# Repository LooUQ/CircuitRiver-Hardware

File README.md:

# CircuitRiver-Hardware
Schematics and PCB layouts for LooUQ Circuit River devices

LooUQ designs and manufactures our Circuit River wireless communications products to make your project range far and wide. Featuring advanced long-distance LTE and LoRa wireless technology and efficient integration with leading development systems and MCU architectures.

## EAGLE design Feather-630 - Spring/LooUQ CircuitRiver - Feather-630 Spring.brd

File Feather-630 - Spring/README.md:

# PCB files for the LooUQ Circuit River Feather-630 Spring 

The LooUQ Circuit River Feather-630 Spring device enables a quick and seemless connection between a Feather form development board (such as Adafruit Feather M0 Express, Adafruit Feather M4 Express, or the SparkFun SAMD51 Things Plus) and any of the LooUQ Circuit River Stream wireless communications circuit boards, when your project also needs a flexible power source. The Feather-630 accepts a DC power source from 6-volts to 30-volts. If you don't need this input voltage flexibility, then consider our Feather-5 Spring; it is less expensive.

The Feather-630 Spring is designed to fit neatly in a [Polycase LP-35F](https://www.polycase.com/lp-35f) or unflanged LP-35P. We left you some room to stuff some sensor or other logic in there too.

EagleCAD format schematic and circuit board layout

For more details, check out the [LooUQ website](http://www.loouq.com) or information in our support desk knowledgebase at [LooUQ Answers Support Desk](http://answers.loouq.com).

Designed by LooUQ
GNU General Public License v3.0, please review the LICENSE file for more information. Commercial private licensing is available, please contact LooUQ via our answers.loouq.com support desk.

Feather form-factor is thanks to Adafruit Industries, see https://adafruit.com
Qwiic sensor connection system is thanks to SparkFun, see https://sparkfun.com

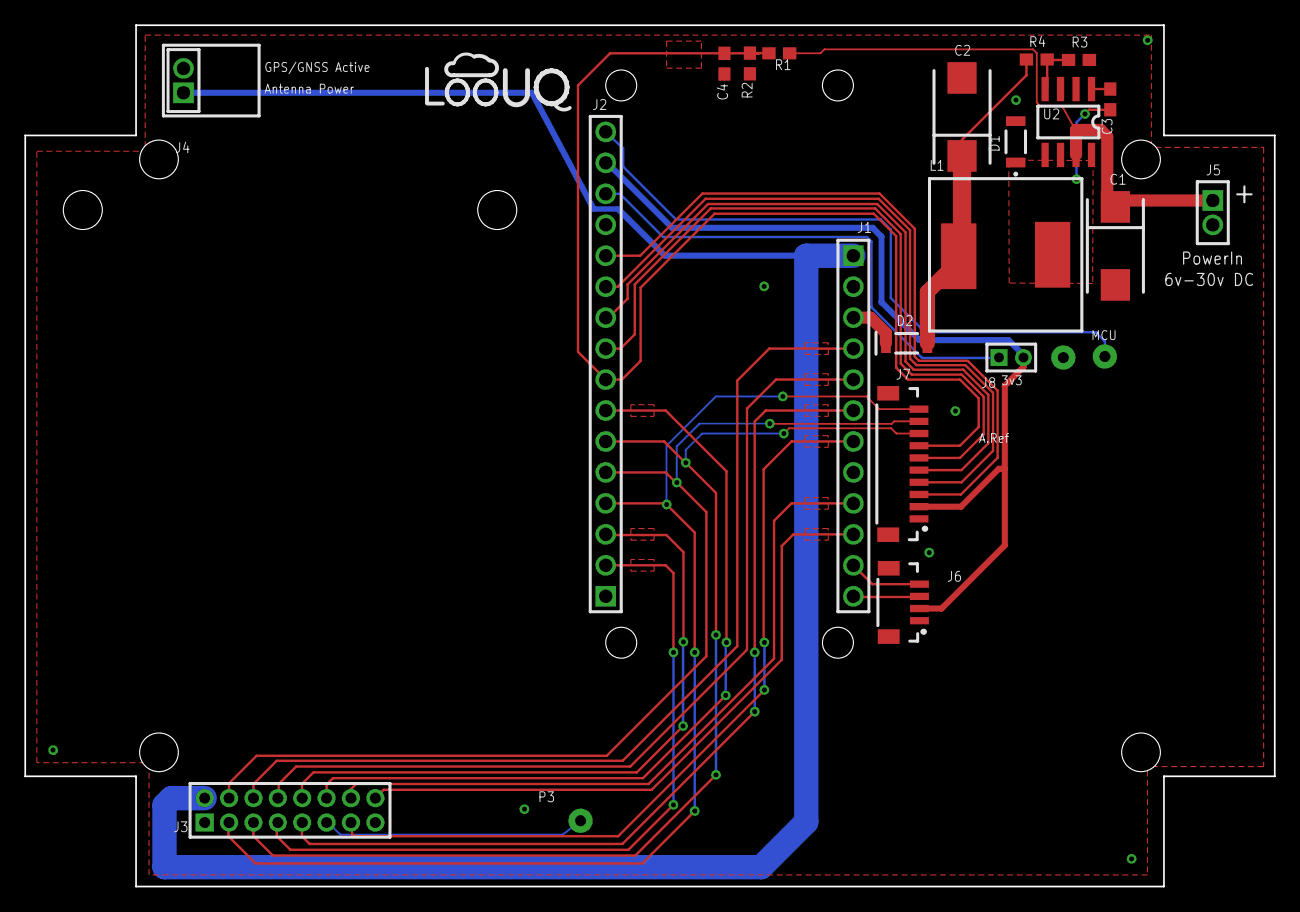
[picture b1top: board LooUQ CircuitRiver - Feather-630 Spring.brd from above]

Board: 2 copper layers, 102.5 x 70.7 mm, 25 parts (1 on the bottom side), 31 nets.

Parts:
C1, C2: 100uF; TC_2917
C3: 10nF; CAP_0603
C4: .1uF; CAP_0603
D1: 1N5819HW; SOD-123
D2: 1N5819HW; SOD-123_D2
J1: FEATHERHOST-S; HDR-1x12T/2.54/30x2
J2: FEATHERHOST-L; HDR-1x16T/2.54/40x2
J3: CR-SPRING HEADER; HDR-2x8T/2x2/16x4
J4: JST PH-2 R/A T/H; JST_PH-2_R/A_T/H
J5: JST PH-2 VERT T/H; JST_PH-2_VERT_T/H
J6: QWIIC VERTICAL; JST_SH-04_VERT_SMD_Qwiic
J7: CR-RAPIDSIO VERTICAL; JST-SH_SMD-TopEntry_Rapids
J8: DNF; HDR-1x2T/2/4x2
L1: 220uH; Bourns_SRR1260_Series
LG1: DNF; LooUQ-6mm
LG2: DNF; CircuitRiver-6mm
P1, P2, P3: DNF; BreakoutConn
R1: 12M; RES_0603
R2: 1.5M; RES_0603
R3: 1.5K; RES_0603
R4: 4.42K; RES_0603
U2: LM2674 BUCK; SOIC-8/150mil

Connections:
Net_1: J1.4, J3.6
Net_2: J2.4, J3.3, J7.10
Net_3v3: J2.15, J6.2, J7.2, J8.2
Net_4: J1.6, J3.9
Net_5: J2.7, J3.12
Net_6: J2.6, J3.5, J7.8
Net_7: J2.3, J3.10
Net_8: J2.5, J3.4, J7.9
Net_9: J1.7, J3.13
Net_10: R3.2, R4.1, U2.4
Net_11: J2.12, J7.3
Net_12: J1.9, J3.14
Net_14: J1.5, J3.8
Net_15: J2.10, J7.5
Net_16: C3.1, U2.1
Net_18: C4.1, J2.8, J7.7, R1.1, R2.1
Net_19: J2.2, J3.7
Net_21: C2.1, D2.2, L1.2, R4.2
Net_22: J3.11, P3.1
Net_23: J2.9, J7.6
Net_25: J2.11, J7.4
Net_26: J1.10, J3.16
Net_27: J1.12, J6.3
Net_28: J1.11, J6.4
Net_29: J2.14, J8.1
Net_30: J2.16, P1.1
Net_GND: C1.2, C2.2, C4.2, D1.2, J2.13, J3.1, J4.2, J5.2, J6.1, J7.1, P2.1, R2.2, R3.1, U2.6
Net_VBAT: J1.1, J3.2, J4.1
Net_VBUS: D2.1, J1.3
Net_VIn: C1.1, J5.1, R1.2, U2.7
Net_VSW: C3.2, D1.1, L1.1, U2.8

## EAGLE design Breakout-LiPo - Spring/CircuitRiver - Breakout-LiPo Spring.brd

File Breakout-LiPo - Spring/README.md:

# PCB files for the LooUQ Circuit River Breakout-LiPo Spring 

The LooUQ Circuit River Breakout-LiPo Spring device makes it easy for you to breadboard with any of the LooUQ Circuit River Stream wireless communications circuit boards and incorporate LiPo battery power in your project. It provides access to all Stream device signals on the breadboard edge header and a robust LiPo battery charger/manager.

EagleCAD format schematic and circuit board layout

For more details, check out the [LooUQ website](http://www.loouq.com) or information in our support desk knowledgebase at [LooUQ Answers Support Desk](http://answers.loouq.com).

Designed by LooUQ
GNU General Public License v3.0, please review the LICENSE file for more information. Commercial private licensing is available, please contact LooUQ via our answers.loouq.com support desk.

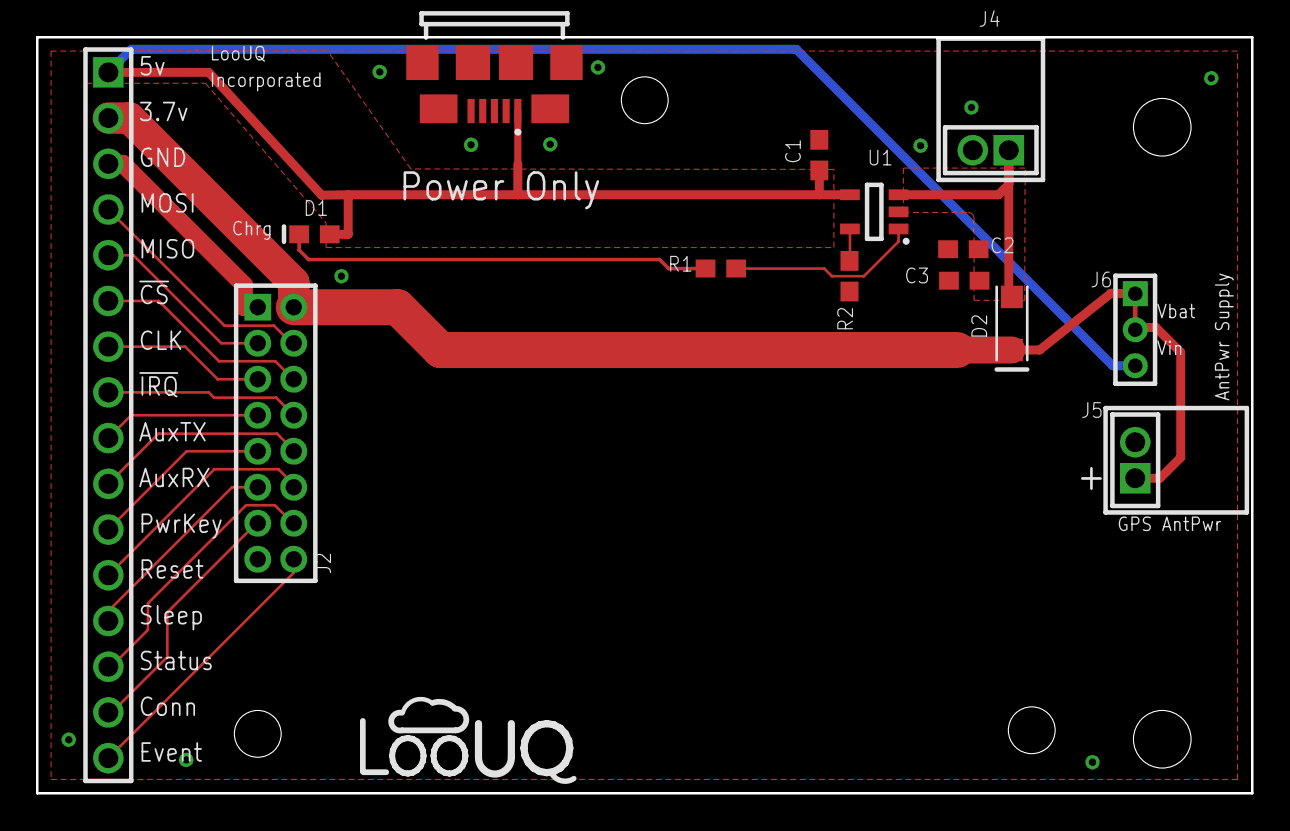
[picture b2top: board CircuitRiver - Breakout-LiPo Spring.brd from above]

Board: 2 copper layers, 67.5 x 42.0 mm, 16 parts (1 on the bottom side), 20 nets.

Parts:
C1, C2: 4.7uF; CAP_0603
C3: 10pF; CAP_0603
D1: Green; LED_0603
D2: SCHOTTKY RECT - 2A60V; SOD-123FL_Diode
J1: DoNotMount; HDR-1x16T/2.54
J2: HA-CTA HEADER; HDR-2x8T/2x2/16x4
J3: USB JACK; ZX62-B-5P
J4: JST PH-2 T/H; JST_PH-2_T/H
J5: JST PH-2 T/H; JST_PH-2_T/H_J5
J6: DNF; HDR-1x3T/2/6x2
LG1: LOOUQ LOGO; LooUQ-6mm
LG2: CIRCUITRIVER LOGO; CircuitRiver-6mm
R1: 470R; RES_0603
R2: 2K; RES_0603
U1: MCP73831-2ACI/OT; SOT23-5

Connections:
Net_0: C1.1, D1.2, J1.1, J3.1, J6.3, U1.4
Net_1: D2.1, J1.2, J2.2, J5.1, J6.1, J6.2
Net_3: J1.16, J2.16
Net_4: J1.15, J2.13
Net_5: J1.14, J2.14
Net_6: J1.13, J2.11
Net_7: J1.12, J2.12
Net_8: J1.11, J2.9
Net_9: J1.10, J2.10
Net_10: J1.9, J2.7
Net_11: J1.8, J2.8
Net_12: J1.7, J2.5
Net_13: J1.6, J2.6
Net_14: J1.5, J2.3
Net_15: J1.4, J2.4
Net_16: C2.1, C3.2, D2.2, J4.1, U1.3
Net_17: R1.2, U1.1
Net_20: R2.2, U1.5
Net_22: D1.1, R1.1
Net_GND: C1.2, C2.2, C3.1, J1.3, J2.1, J3.5, J3.6, J4.2, J5.2, R2.1, U1.2

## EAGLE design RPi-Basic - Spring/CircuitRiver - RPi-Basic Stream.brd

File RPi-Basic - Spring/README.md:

# PCB files for the LooUQ Circuit River RPi-Basic Spring 

The LooUQ Circuit River RPi-Basic Spring device enables a quick and seemless connection between a Raspberry PI 3 or 4 and any of the LooUQ Circuit River Stream wireless communications circuit boards.

EagleCAD format schematic and circuit board layout

For more details, check out the [LooUQ website](http://www.loouq.com) or information in our support desk knowledgebase at [LooUQ Answers Support Desk](http://answers.loouq.com).

Designed by LooUQ
GNU General Public License v3.0, please review the LICENSE file for more information. Commercial private licensing is available, please contact LooUQ via our answers.loouq.com support desk.

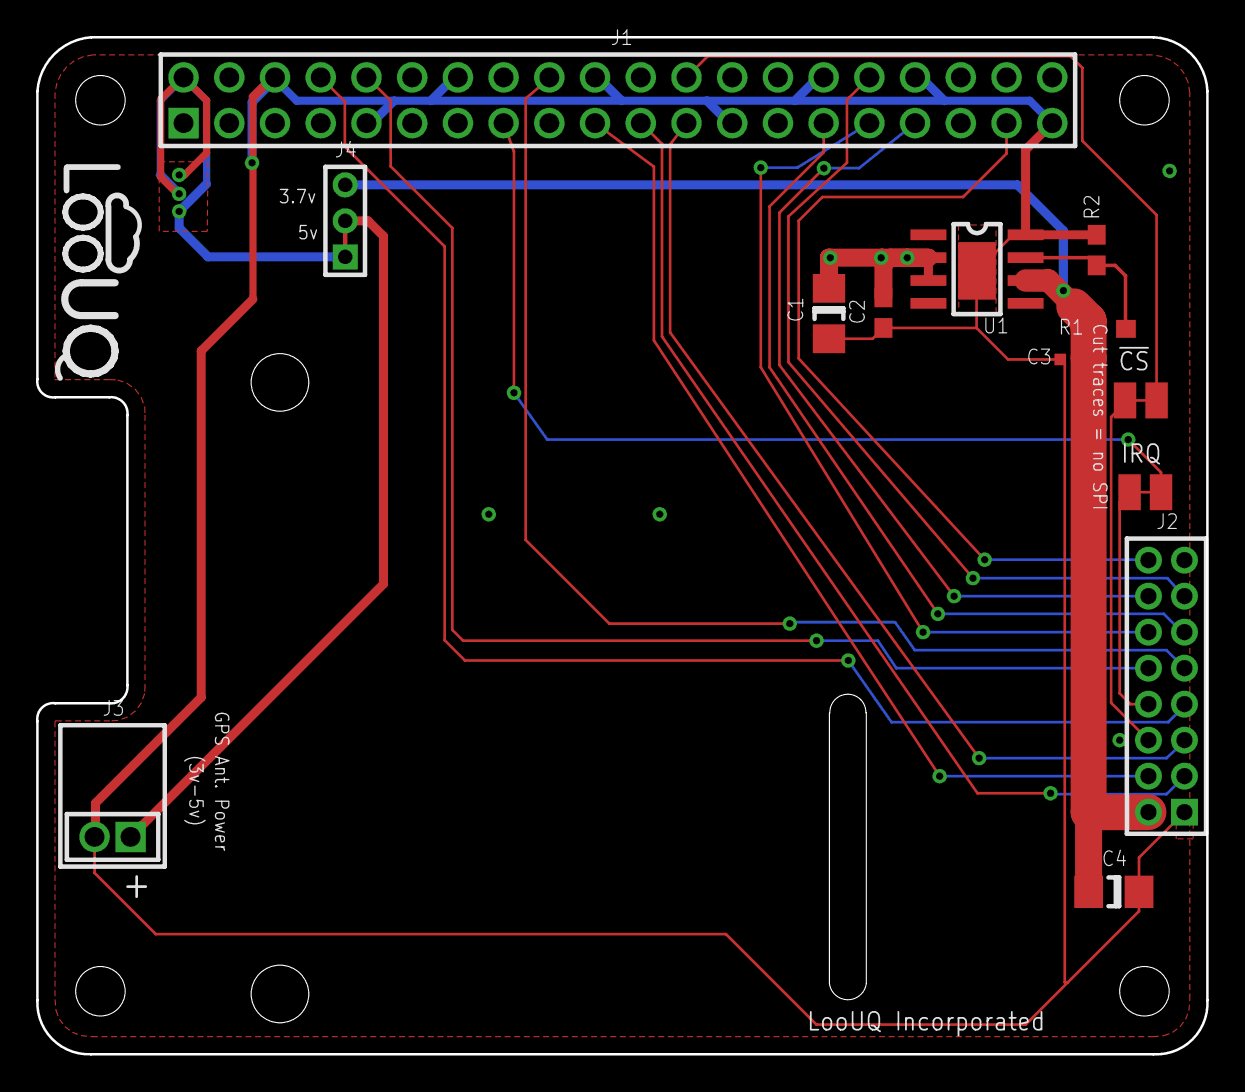
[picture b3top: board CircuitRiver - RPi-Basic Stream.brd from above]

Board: 2 copper layers, 65.0 x 56.5 mm, 16 parts (1 on the bottom side), 17 nets.

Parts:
C1: 220uF; CAP_1206
C2: 10uF; CAP_0603
C3: 0.1uF; 0402_NP
C4: 220uF; CAP_1206_C4
J1: R-PI GPIO HEADER; HDR-2x20T/2.54x2.54/51x5
J2: STREAM CONNECTION; HDR-2x8T/2x2/16x4
J3: JST PH-2 T/H; JST_PH-2_T/H
J4: DNF; HDR-1x3T/2/6x2
Keepout_1: 1; ROUTE_KEEPOUT_1
LG1: LOOUQ LOGO; LooUQ-6mm
LG2: CIRCUITRIVER LOGO; CircuitRiver-6mm
R1: 10K; RES_0603
R2: 1.5K; RES_0603
TJ1, TJ2: NoMount; TraceJumper
U1: SC4215HSETRT; SOIC-8EP/150mil

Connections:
GND: C1.2, C2.1, C3.1, C4.1, J1.6, J1.9, J1.14, J1.20, J1.25, J1.30, J1.34, J1.39, J2.1, J3.2, R2.1, U1.8, U1.9
Net_2: R1.1, R2.2, U1.7
Net_4: J1.19, J2.4
Net_5: J1.21, J2.3
Net_6: J1.23, J2.5
Net_7: J1.24, J2.6, TJ1.1, TJ1.2
Net_8: J1.31, J2.12
Net_9: J1.33, J2.14
Net_10: J1.18, J2.9
Net_11: J1.15, J2.8, TJ2.1, TJ2.2
Net_12: J1.8, J2.7
Net_13: J1.10, J2.10
Net_14: J1.29, J2.11
Net_15: J1.32, J2.13
Net_16: J1.37, J2.16
Pwr5v0: C1.1, C2.2, J1.2, J3.1, J4.1, J4.2, U1.2, U1.3
VBAT: C3.2, C4.2, J2.2, J4.3, R1.2, U1.6

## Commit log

2019-08-01 Create LICENSE
2019-08-01 Updated files for RPi-Basic
2019-08-01 Updated Eagles and readme text
2019-08-03 Added Feather-630
2019-08-03 Updates for Feather-630
2019-08-08 updated with CircuitRiver RapidsIO connector
2019-08-08 Added Feather-5 and updates to readme.md
2019-08-09 Updated Feathers
2019-08-10 Moved RapidsIO, chg L1 on F-630
2019-08-10 added schematic PDF files
